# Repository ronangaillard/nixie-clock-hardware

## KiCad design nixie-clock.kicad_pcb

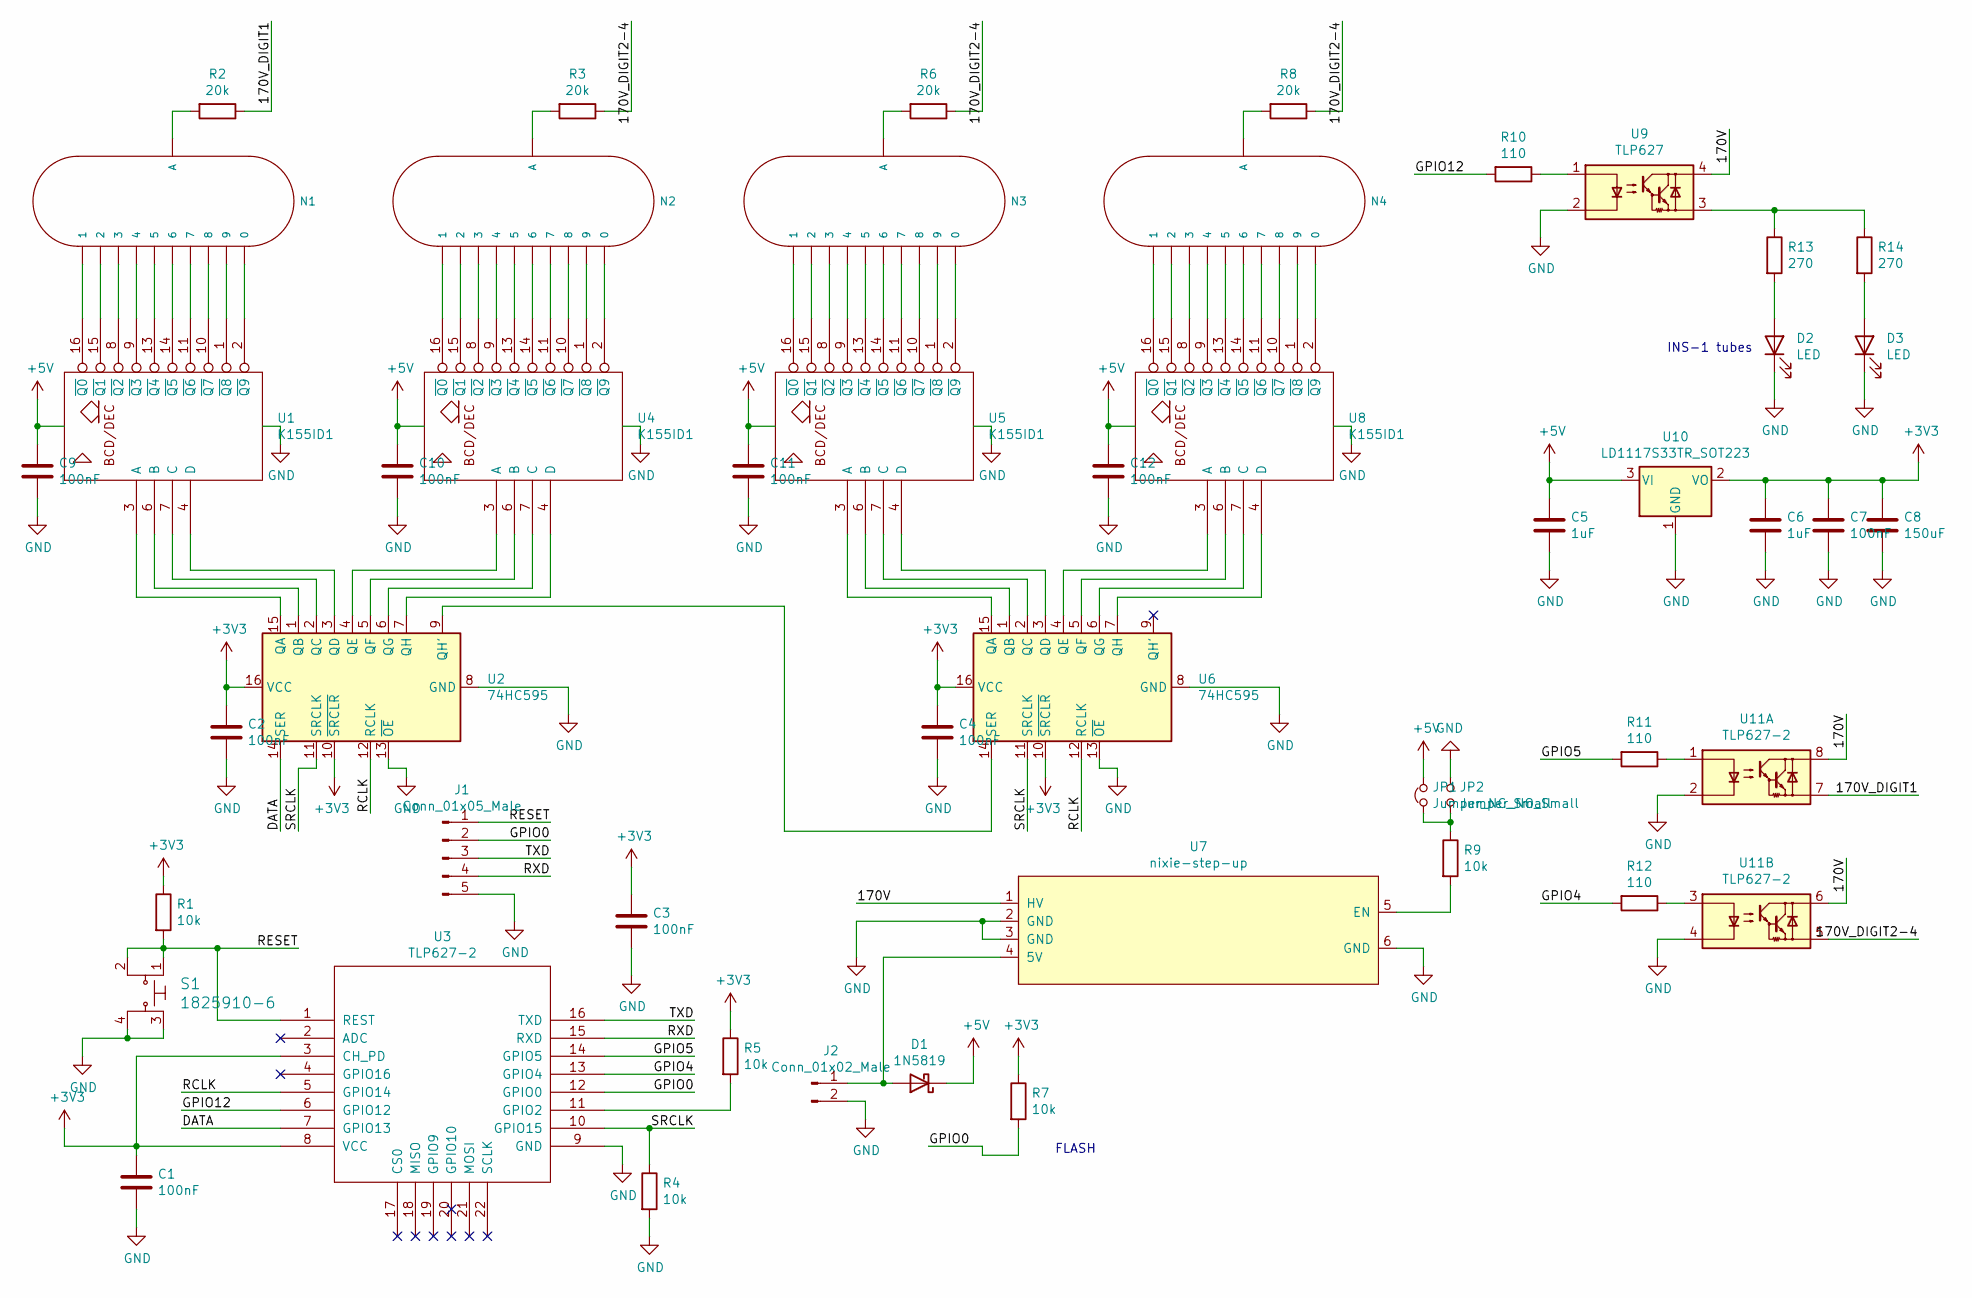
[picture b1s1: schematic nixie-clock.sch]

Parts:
C1, C2, C3, C4, C7, C9, C10, C11, C12: 100nF; C_1206_3216Metric_Pad1.42x1.75mm_HandSolder
C5, C6: 1uF; C_1206_3216Metric_Pad1.42x1.75mm_HandSolder
C8: 150uF; C_1206_3216Metric_Pad1.42x1.75mm_HandSolder
D1: 1N5819; D_SOD-323_HandSoldering
D2, D3: LED; LED_D5.0mm_Clear
J1: Conn_01x05_Male; PinHeader_1x05_P2.54mm_Vertical
J2: Conn_01x02_Male; PinHeader_1x02_P2.54mm_Vertical
JP1: Jumper_NC_Small; SolderJumper-2_P1.3mm_Bridged_RoundedPad1.0x1.5mm
JP2: Jumper_NO_Small; SolderJumper-2_P1.3mm_Open_RoundedPad1.0x1.5mm
N1, N2, N3, N4: IN-4; IN-4-DSUB
R1, R4, R5, R7, R9: 10k; R_1206_3216Metric_Pad1.42x1.75mm_HandSolder
R2, R3, R6, R8: 20k; R_1206_3216Metric_Pad1.42x1.75mm_HandSolder
R10, R11, R12: 110; R_1206_3216Metric_Pad1.42x1.75mm_HandSolder
R13, R14: 270; R_1206_3216Metric_Pad1.42x1.75mm_HandSolder
S1: 1825910-6; Switch_Tactile_THT_6x6mm; MPN 1825910-6; Digi-Key_PN 450-1650-ND
U1, U4, U5, U8: K155ID1; DIP-16_W7.62mm
U2, U6: 74HC595; DIP-16_W7.62mm
U3: TLP627-2; ESP-12E
U7: nixie-step-up
U9: TLP627; DIP-4_W7.62mm
U10: LD1117S33TR_SOT223; SOT-223-3_TabPin2
U11: TLP627-2; DIP-8_W7.62mm

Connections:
+3V3: C1.1, C2.1, C3.1, C4.1, C6.1, C7.1, C8.1, R1.1, R5.1, R7.1, U2.10 (~SRCLR), U2.16 (VCC), U3.3 (CH_PD), U3.8 (VCC), U6.10 (~SRCLR), U6.16 (VCC), U10.2 (VO)
+5V: C5.1, C9.1, C10.1, C11.1, C12.1, D1.1 (K), JP1.2, U1.5 (VCC), U4.5 (VCC), U5.5 (VCC), U8.5 (VCC), U10.3 (VI)
/170V: U7.1 (HV), U9.4, U11.6, U11.8
/170V_DIGIT1: R2.1, U11.7
/170V_DIGIT2-4: R3.1, R6.1, R8.1, U11.5
/DATA: U2.14 (SER), U3.7 (GPIO13)
/GPIO0: J1.2, R7.2, U3.12 (GPIO0)
/GPIO4: R12.2, U3.13 (GPIO4)
/GPIO5: R11.2, U3.14 (GPIO5)
/GPIO12: R10.2, U3.6 (GPIO12)
/RCLK: U2.12 (RCLK), U3.5 (GPIO14), U6.12 (RCLK)
/RESET: J1.1, R1.2, S1.1, S1.2, U3.1 (REST)
/RXD: J1.4, U3.15 (RXD)
/SRCLK: R4.1, U2.11 (SRCLK), U3.10 (GPIO15), U6.11 (SRCLK)
/TXD: J1.3, U3.16 (TXD)
GND: C1.2, C2.2, C3.2, C4.2, C5.2, C6.2, C7.2, C8.2, C9.2, C10.2, C11.2, C12.2, D2.1 (K), D3.1 (K), J1.5, J2.2, JP2.1, R4.2, S1.3, S1.4, U1.12 (GND), U2.8 (GND), U2.13 (~OE), U3.9 (GND), U4.12 (GND), U5.12 (GND), U6.8 (GND), U6.13 (~OE), U7.2 (GND), U7.3 (GND), U7.6 (GND), U8.12 (GND), U9.2, U10.1 (GND), U11.2, U11.4
unnamed: D1.2 (A), J2.1, U7.4 (5V)
unnamed: D2.2 (A), R13.2
unnamed: D3.2 (A), R14.2
unnamed: JP1.1, JP2.2, R9.1
unnamed: N1.0, U1.2 (~Q9)
unnamed: N1.1, U1.16 (~Q0)
unnamed: N1.2, U1.15 (~Q1)
unnamed: N1.3, U1.8 (~Q2)
unnamed: N1.4, U1.9 (~Q3)
unnamed: N1.5, U1.13 (~Q4)
unnamed: N1.6, U1.14 (~Q5)
unnamed: N1.7, U1.11 (~Q6)
unnamed: N1.8, U1.10 (~Q7)
unnamed: N1.9, U1.1 (~Q8)
unnamed: N1.A3 (A), R2.2
unnamed: N2.0, U4.2 (~Q9)
unnamed: N2.1, U4.16 (~Q0)
unnamed: N2.2, U4.15 (~Q1)
unnamed: N2.3, U4.8 (~Q2)
unnamed: N2.4, U4.9 (~Q3)
unnamed: N2.5, U4.13 (~Q4)
unnamed: N2.6, U4.14 (~Q5)
unnamed: N2.7, U4.11 (~Q6)
unnamed: N2.8, U4.10 (~Q7)
unnamed: N2.9, U4.1 (~Q8)
unnamed: N2.A3 (A), R3.2
unnamed: N3.0, U5.2 (~Q9)
unnamed: N3.1, U5.16 (~Q0)
unnamed: N3.2, U5.15 (~Q1)
unnamed: N3.3, U5.8 (~Q2)
unnamed: N3.4, U5.9 (~Q3)
unnamed: N3.5, U5.13 (~Q4)
unnamed: N3.6, U5.14 (~Q5)
unnamed: N3.7, U5.11 (~Q6)
unnamed: N3.8, U5.10 (~Q7)
unnamed: N3.9, U5.1 (~Q8)
unnamed: N3.A3 (A), R6.2
unnamed: N4.0, U8.2 (~Q9)
unnamed: N4.1, U8.16 (~Q0)
unnamed: N4.2, U8.15 (~Q1)
unnamed: N4.3, U8.8 (~Q2)
unnamed: N4.4, U8.9 (~Q3)
unnamed: N4.5, U8.13 (~Q4)
unnamed: N4.6, U8.14 (~Q5)
unnamed: N4.7, U8.11 (~Q6)
unnamed: N4.8, U8.10 (~Q7)
unnamed: N4.9, U8.1 (~Q8)
unnamed: N4.A3 (A), R8.2
unnamed: R5.2, U3.11 (GPIO2)
unnamed: R9.2, U7.5 (EN)
unnamed: R10.1, U9.1
unnamed: R11.1, U11.1
unnamed: R12.1, U11.3
unnamed: R13.1, R14.1, U9.3
unnamed: U1.3 (A), U2.15 (QA)
unnamed: U1.4 (D), U2.3 (QD)
unnamed: U1.6 (B), U2.1 (QB)
unnamed: U1.7 (C), U2.2 (QC)
unnamed: U2.4 (QE), U4.3 (A)
unnamed: U2.5 (QF), U4.6 (B)
unnamed: U2.6 (QG), U4.7 (C)
unnamed: U2.7 (QH), U4.4 (D)
unnamed: U2.9 (QH'), U6.14 (SER)
unnamed: U5.3 (A), U6.15 (QA)
unnamed: U5.4 (D), U6.3 (QD)
unnamed: U5.6 (B), U6.1 (QB)
unnamed: U5.7 (C), U6.2 (QC)
unnamed: U6.4 (QE), U8.3 (A)
unnamed: U6.5 (QF), U8.6 (B)
unnamed: U6.6 (QG), U8.7 (C)
unnamed: U6.7 (QH), U8.4 (D)

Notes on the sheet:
INS-1 tubes
FLASH

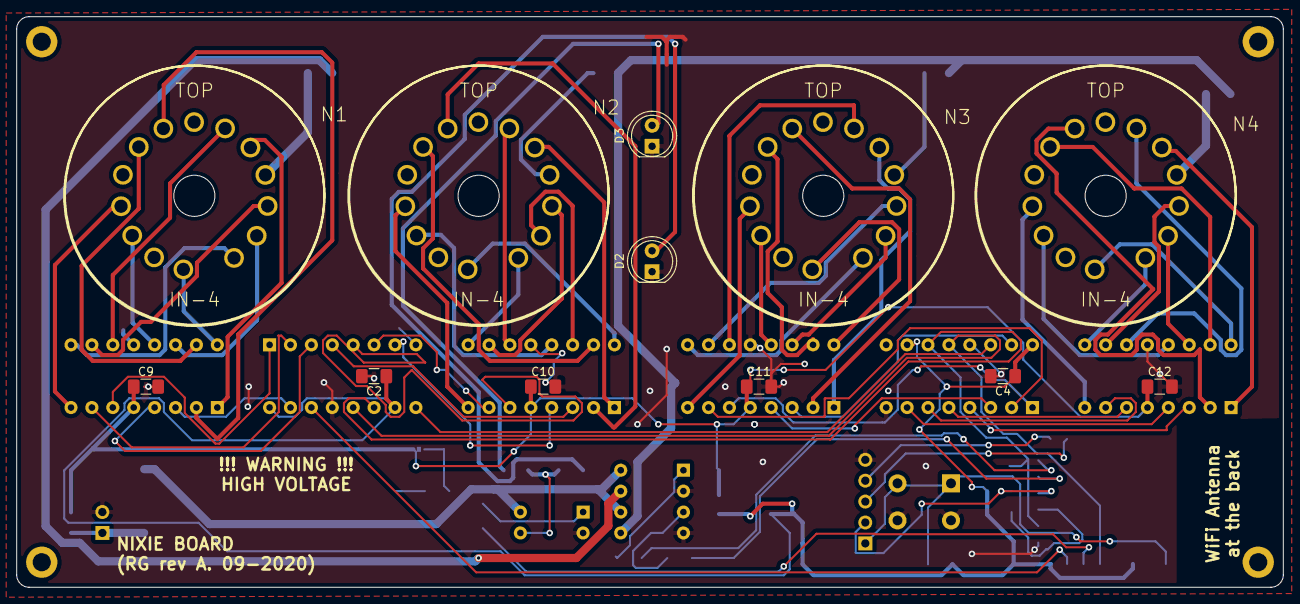
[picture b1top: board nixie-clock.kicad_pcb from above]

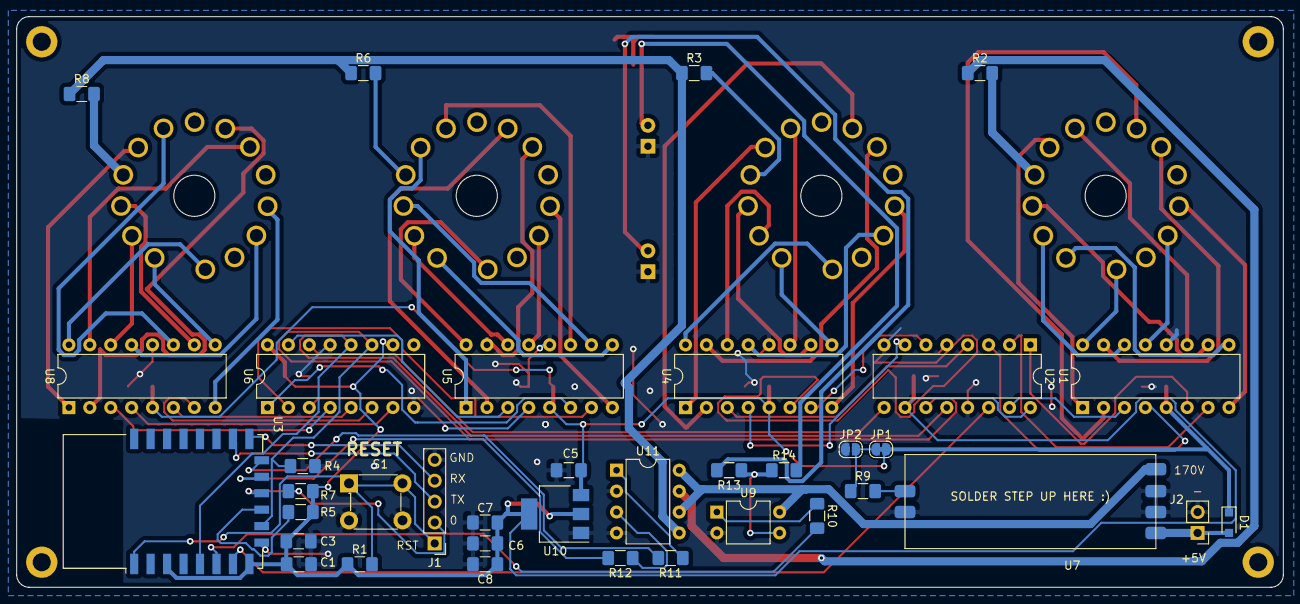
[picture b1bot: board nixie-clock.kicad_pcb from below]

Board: 2 copper layers, 153.9 x 69.3 mm, 49 parts (37 on the bottom side), 87 nets.

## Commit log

2020-09-06 finish rev a
2020-09-09 Fix alignment on main board and add front and back board
